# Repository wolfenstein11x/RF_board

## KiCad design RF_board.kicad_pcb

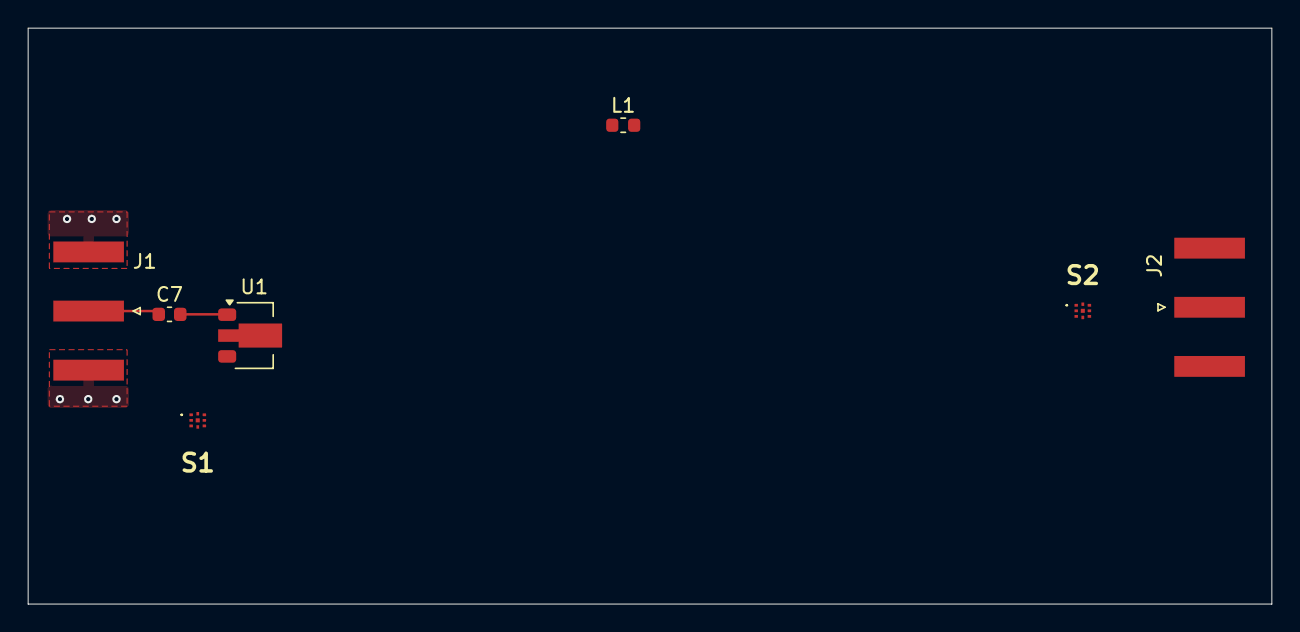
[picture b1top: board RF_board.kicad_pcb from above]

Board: 4 copper layers, 89.4 x 41.4 mm, 7 parts (0 on the bottom side), 5 nets.

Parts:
C7: 1n; C_0603_1608Metric
J1, J2: Conn_Coaxial; SMA_Amphenol_132289_EdgeMount
L1: 6.2n; L_0603_1608Metric
S1, S2: SKY13586-678LF; SKY13586678LF
U1: SPF5189Z; SOT-89-3

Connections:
/RF_amped: S1.1 (RFC), U1.3
/RF_decop: C7.2, U1.1
/RF_in: C7.1, J1.1 (In)
GND: J1.2 (Ext), J2.1 (In), L1.2, S1.8 (GND_1), S1.9 (GND_2), U1.2 (GND_2)
unnamed: J2.2 (Ext), S2.1 (RFC_1)
